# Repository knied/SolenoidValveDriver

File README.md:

# SolenoidValveDriver
A PCB to drive Festo MH1 solenoid valves with a "USBIO24 R" (https://www.robotshop.com/de/en/elexol-usb-digital-interface-usbio24-r.html)

Symbol | Part | Link
------ | ---- | ----
Q1-Q8 | IRFU024N | https://www.infineon.com/cms/en/product/power/mosfet/12v-300v-n-channel-power-mosfet/irfu024n/
R1-R9 | 220 Ohm |
R10-R17 | 100 Ohm | 
R18-R25 | 100k Ohm |
D1-D9 | 5mm Red LED |
D10-D17 | 1N4937 | https://www.vishay.com/docs/88508/1n4933.pdf
D18-D25 | 1N4748 | https://www.futurlec.com/Diodes/1N4748.shtml
C1 | 100uF |
J1 | 16x TerminalBlock (5.08mm) |
J2 | 2x TerminalBlock (5.08mm) |
J3 | 2x5 Pin Header (2.54mm) |

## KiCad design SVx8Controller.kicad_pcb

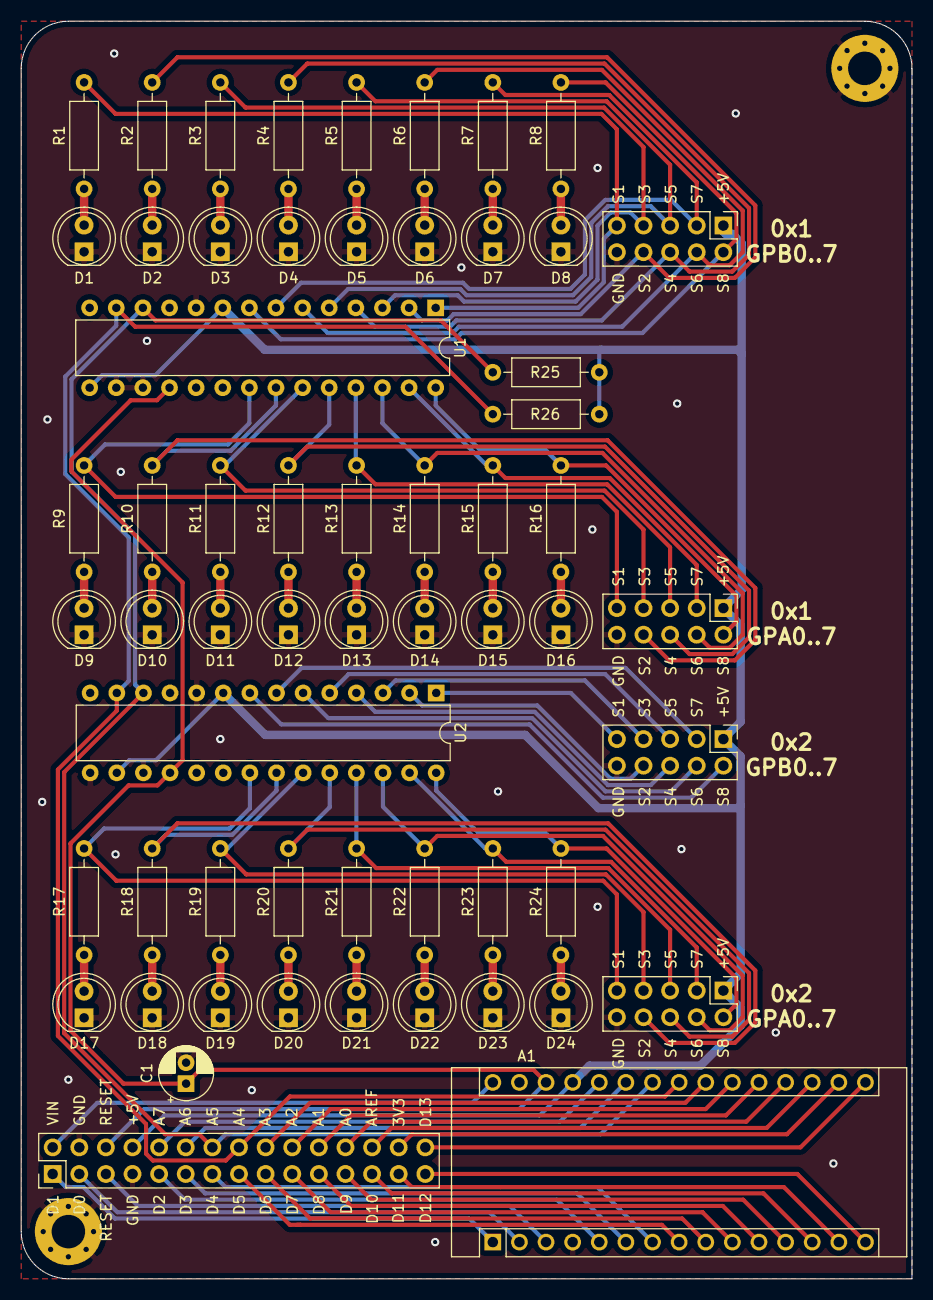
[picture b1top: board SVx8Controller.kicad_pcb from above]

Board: 2 copper layers, 85.0 x 120.0 mm, 61 parts (0 on the bottom side), 85 nets.

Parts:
A1: Arduino_Nano_v3.x; Arduino_Nano
C1: 10uF; CP_Radial_D5.0mm_P2.00mm
D1, D2, D3, D4, D5, D6, D7, D8, D9, D10, D11, D12, D13, D14, D15, D16, D17, D18, D19, D20, D21, D22, D23, D24: LED; LED_D5.0mm
H1, H2: MountingHole_Pad; MountingHole_3.2mm_M3_Pad_Via
J1, J2, J3: Output; PinHeader_2x05_P2.54mm_Vertical
J4: Conn_01x10; PinHeader_2x05_P2.54mm_Vertical
J5: Conn_01x30; PinHeader_2x15_P2.54mm_Vertical
R1, R2, R3, R4, R5, R6, R7, R8, R9, R10, R11, R12, R13, R14, R15, R16, R17, R18, R19, R20, R21, R22, R23, R24: 220; R_Axial_DIN0207_L6.3mm_D2.5mm_P10.16mm_Horizontal
R25, R26: 10K; R_Axial_DIN0207_L6.3mm_D2.5mm_P10.16mm_Horizontal
U1, U2: MCP23017_SP; DIP-28_W7.62mm

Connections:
3V3: A1.17, J5.28
5V: A1.27, J1.1, J2.1, J3.1, J4.1, J5.8, R25.2, R26.2, U1.9, U1.15, U2.9, U2.16
/Port A/SIG1: J1.9, R9.2, U1.21
/Port A/SIG2: J1.8, R10.2, U1.22
/Port A/SIG3: J1.7, R11.2, U1.23
/Port A/SIG4: J1.6, R12.2, U1.24
/Port A/SIG5: J1.5, R13.2, U1.25
/Port A/SIG6: J1.4, R14.2, U1.26
/Port A/SIG7: J1.3, R15.2, U1.27
/Port A/SIG8: J1.2, R16.2, U1.28
/Port B/SIG1: J2.9, R1.2, U1.1
/Port B/SIG2: J2.8, R2.2, U1.2
/Port B/SIG3: J2.7, R3.2, U1.3
/Port B/SIG4: J2.6, R4.2, U1.4
/Port B/SIG5: J2.5, R5.2, U1.5
/Port B/SIG6: J2.4, R6.2, U1.6
/Port B/SIG7: J2.3, R7.2, U1.7
/Port B/SIG8: J2.2, R8.2, U1.8
/Port C/SIG1: J3.9, R17.2, U2.21
/Port C/SIG2: J3.8, R18.2, U2.22
/Port C/SIG3: J3.7, R19.2, U2.23
/Port C/SIG4: J3.6, R20.2, U2.24
/Port C/SIG5: J3.5, R21.2, U2.25
/Port C/SIG6: J3.4, R22.2, U2.26
/Port C/SIG7: J3.3, R23.2, U2.27
/Port C/SIG8: J3.2, R24.2, U2.28
A0: A1.19, J5.24
A1: A1.20, J5.22
A2: A1.21, J5.20
A3: A1.22, J5.18
A4: A1.23, J5.16, R26.1, U1.13, U2.13
A5: A1.24, J5.14, R25.1, U1.12, U2.12
A6: A1.25, J5.12
A7: A1.26, J5.10
AREF: A1.18, J5.26
D0: A1.2, J5.3
D1: A1.1, J5.1
D2: A1.5, J5.9
D3: A1.6, J5.11
D4: A1.7, J5.13
D5: A1.8, J5.15
D6: A1.9, J5.17
D7: A1.10, J5.19
D8: A1.11, J5.21
D9: A1.12, J5.23
D10: A1.13, J5.25
D11: A1.14, J5.27
D12: A1.15, J5.29
D13: A1.16, J5.30
GND: A1.4, A1.29, C1.2, D1.1, D2.1, D3.1, D4.1, D5.1, D6.1, D7.1, D8.1, D9.1, D10.1, D11.1, D12.1, D13.1, D14.1, D15.1, D16.1, D17.1, D18.1, D19.1, D20.1, D21.1, D22.1, D23.1, D24.1, H1.1, H2.1, J1.10, J2.10, J3.10, J4.10, J5.4, J5.7, U1.10, U1.16, U1.17, U2.10, U2.15, U2.17
unnamed: D1.2, R1.1
unnamed: D2.2, R2.1
unnamed: D3.2, R3.1
unnamed: D4.2, R4.1
unnamed: D5.2, R5.1
unnamed: D6.2, R6.1
unnamed: D7.2, R7.1
unnamed: D8.2, R8.1
unnamed: D9.2, R9.1
unnamed: D10.2, R10.1
unnamed: D11.2, R11.1
unnamed: D12.2, R12.1
unnamed: D13.2, R13.1
unnamed: D14.2, R14.1
unnamed: D15.2, R15.1
unnamed: D16.2, R16.1
unnamed: D17.2, R17.1
unnamed: D18.2, R18.1
unnamed: D19.2, R19.1
unnamed: D20.2, R20.1
unnamed: D21.2, R21.1
unnamed: D22.2, R22.1
unnamed: D23.2, R23.1
unnamed: D24.2, R24.1
PD1: J4.9, U2.1
PD2: J4.8, U2.2
PD3: J4.7, U2.3
PD4: J4.6, U2.4
PD5: J4.5, U2.5
PD6: J4.4, U2.6
PD7: J4.3, U2.7
PD8: J4.2, U2.8
RESET: A1.28, C1.1, J5.6, U1.18, U2.18
RESET2: A1.3, J5.5
VIN: A1.30, J5.2

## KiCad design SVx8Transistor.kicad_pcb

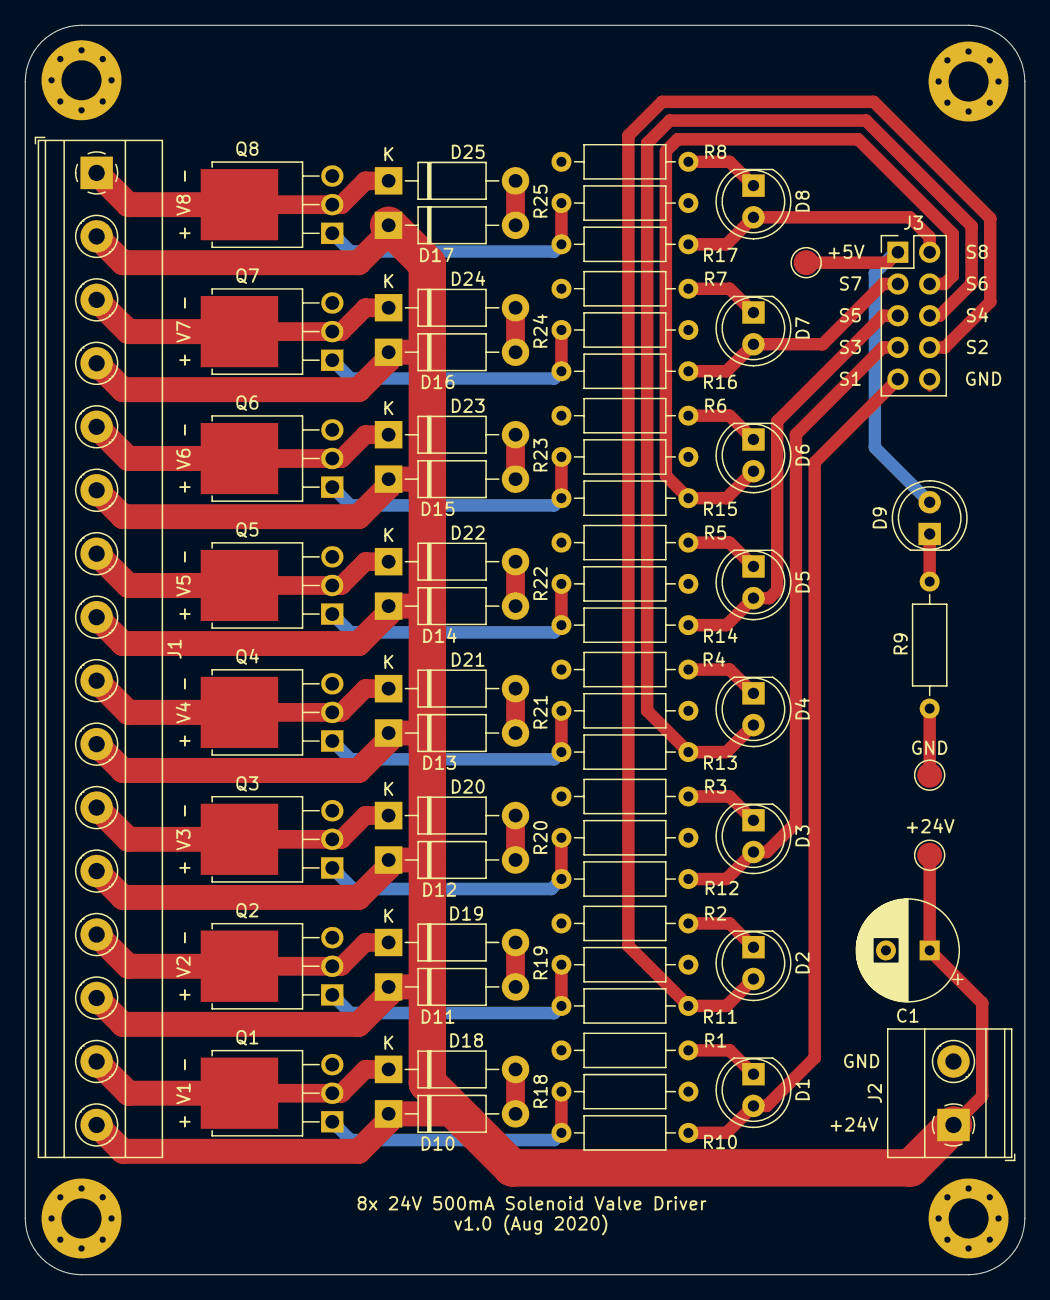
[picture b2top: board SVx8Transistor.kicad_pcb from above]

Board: 2 copper layers, 80.0 x 100.0 mm, 69 parts (0 on the bottom side), 44 nets.

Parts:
C1: 100uF; CP_Radial_D8.0mm_P3.50mm
D1, D2, D3, D4, D5, D6, D7, D8, D9: LED; LED_D5.0mm
D10, D11, D12, D13, D14, D15, D16, D17: 1N4937; D_DO-41_SOD81_P10.16mm_Horizontal
D18, D19, D20, D21, D22, D23, D24, D25: 1N4748; D_DO-41_SOD81_P10.16mm_Horizontal
H1, H2, H3, H4: MountingHole_Pad; MountingHole_3.2mm_M3_Pad_Via
J1: Valves; TerminalBlock_Phoenix_MKDS-1,5-16-5.08_1x16_P5.08mm_Horizon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
J2: Power; TerminalBlock_Phoenix_MKDS-1,5-2-5.08_1x02_P5.08mm_Horizont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
J3: Signals; PinHeader_2x05_P2.54mm_Vertical
Q1, Q2, Q3, Q4, Q5, Q6, Q7, Q8: IRFU024N; TO-251-3-1EP_Horizontal_TabDown
R1, R2, R3, R4, R5, R6, R7, R8, R9: 220; R_Axial_DIN0207_L6.3mm_D2.5mm_P10.16mm_Horizontal
R10, R11, R12, R13, R14, R15, R16, R17: 100; R_Axial_DIN0207_L6.3mm_D2.5mm_P10.16mm_Horizontal
R18, R19, R20, R21, R22, R23, R24, R25: 100k; R_Axial_DIN0207_L6.3mm_D2.5mm_P10.16mm_Horizontal
TP1: GND; TestPoint_Pad_D2.0mm
TP2: +24V; TestPoint_Pad_D2.0mm
TP3: +5V; TestPoint_Pad_D2.0mm

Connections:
5V: D9.2, J3.1, TP3.1
GND: C1.2, H1.1, H2.1, H3.1, H4.1, J2.2, J3.10, Q1.3, Q2.3, Q3.3, Q4.3, Q5.3, Q6.3, Q7.3, Q8.3, R1.2, R2.2, R3.2, R4.2, R5.2, R6.2, R7.2, R8.2, R9.2, R18.2, R19.2, R20.2, R21.2, R22.2, R23.2, R24.2, R25.2, TP1.1
unnamed: D1.1, R1.1
unnamed: D2.1, R2.1
unnamed: D3.1, R3.1
unnamed: D4.1, R4.1
unnamed: D5.1, R5.1
unnamed: D6.1, R6.1
unnamed: D7.1, R7.1
unnamed: D8.1, R8.1
unnamed: D9.1, R9.1
unnamed: D10.2, D18.2
unnamed: D11.2, D19.2
unnamed: D12.2, D20.2
unnamed: D13.2, D21.2
unnamed: D14.2, D22.2
unnamed: D15.2, D23.2
unnamed: D16.2, D24.2
unnamed: D17.2, D25.2
unnamed: Q1.1, R10.1, R18.1
unnamed: Q2.1, R11.1, R19.1
unnamed: Q3.1, R12.1, R20.1
unnamed: Q4.1, R13.1, R21.1
unnamed: Q5.1, R14.1, R22.1
unnamed: Q6.1, R15.1, R23.1
unnamed: Q7.1, R16.1, R24.1
unnamed: Q8.1, R17.1, R25.1
SIG1: D1.2, J3.9, R10.2
SIG2: D2.2, J3.8, R11.2
SIG3: D3.2, J3.7, R12.2
SIG4: D4.2, J3.6, R13.2
SIG5: D5.2, J3.5, R14.2
SIG6: D6.2, J3.4, R15.2
SIG7: D7.2, J3.3, R16.2
SIG8: D8.2, J3.2, R17.2
VCC: C1.1, D10.1, D11.1, D12.1, D13.1, D14.1, D15.1, D16.1, D17.1, J1.2, J1.4, J1.6, J1.8, J1.10, J1.12, J1.14, J1.16, J2.1, TP2.1
Valve1_Black: D18.1, J1.15, Q1.2, Q1.4
Valve2_Black: D19.1, J1.13, Q2.2, Q2.4
Valve3_Black: D20.1, J1.11, Q3.2, Q3.4
Valve4_Black: D21.1, J1.9, Q4.2, Q4.4
Valve5_Black: D22.1, J1.7, Q5.2, Q5.4
Valve6_Black: D23.1, J1.5, Q6.2, Q6.4
Valve7_Black: D24.1, J1.3, Q7.2, Q7.4
Valve8_Black: D25.1, J1.1, Q8.2, Q8.4

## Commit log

2020-09-12 photos
2024-12-27 Add controller front plate
2024-12-28 Fix pin header
2025-01-11 Add pull-up resistors
2025-01-11 Add a controller PCB (#1)
    * Add controller front plate
    * Fix pin header
    * Add pull-up resistors
2025-01-11 Fix edge cut widths
2025-02-03 Add a program for the Arduino Nano
    It mimics the behavior of a USBIO24.
